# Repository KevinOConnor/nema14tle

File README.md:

This is an experimental pcb design for a TLE5012B angle sensor mounted
on the back of a NEMA14 stepper motor.

This is an experiment. There is no support for this project.

The original design of the board is from Voron user "JNP".

The PCB design files can be found in the [pcb/](pcb/) directory.  The
boards were designed using [KiCad](https://kicad.org/) and
manufactured using [JLC PCB](https://jlcpcb.com/).

There is some information on the magnet mounting procedure in the
[magnet document](docs/magnet.md).

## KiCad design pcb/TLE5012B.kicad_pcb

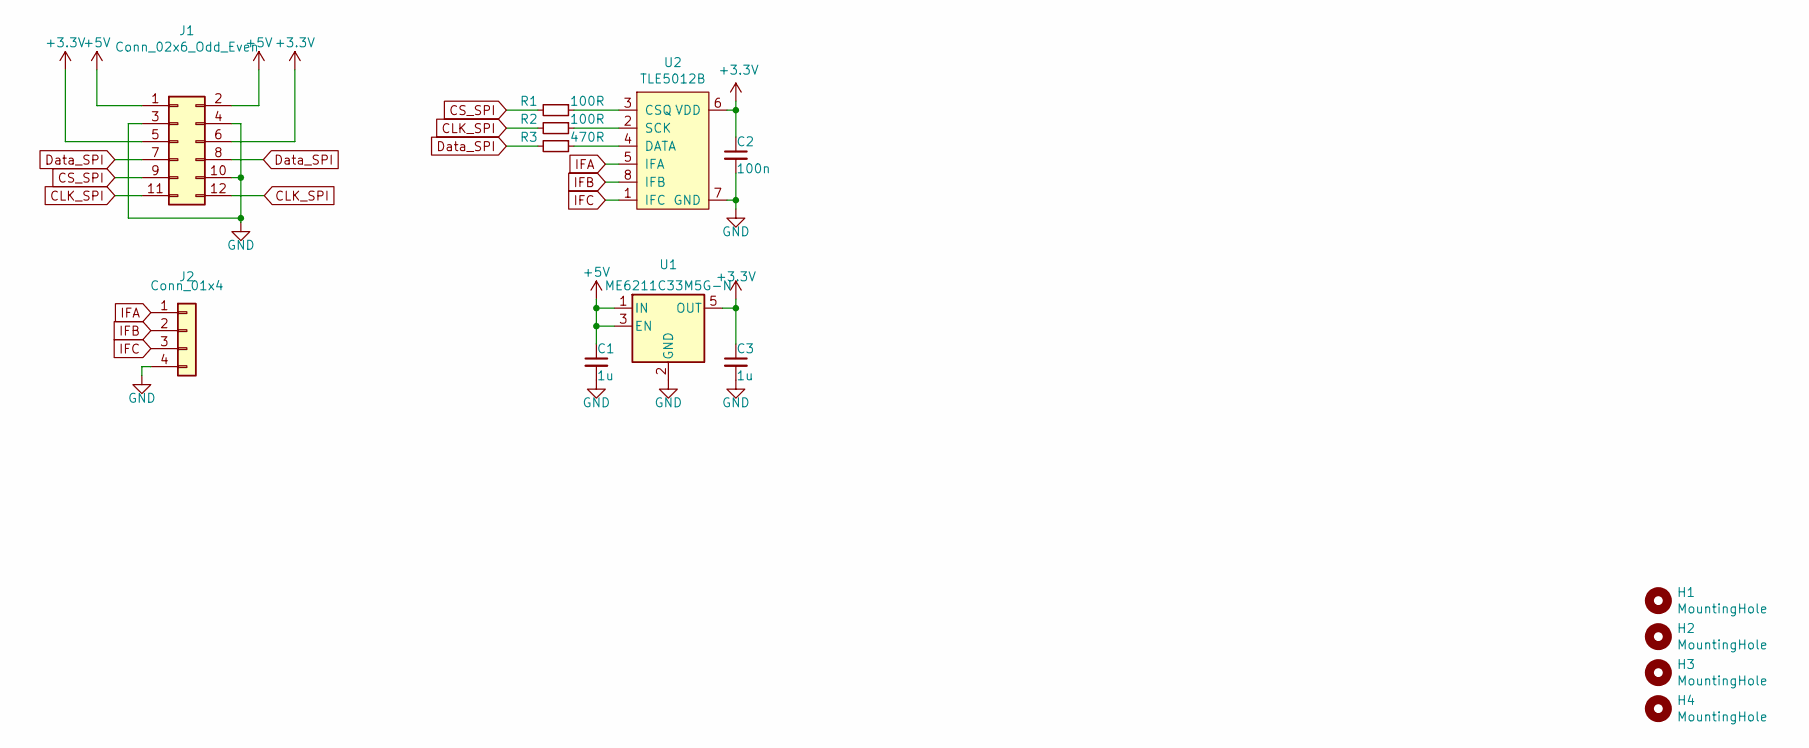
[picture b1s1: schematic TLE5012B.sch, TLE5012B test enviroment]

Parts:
C1, C3: 1u; C_0603_1608Metric; MFG# 0603B105K250NT; LCSC# C59302
C2: 100n; C_0603_1608Metric; LCSC# C14663
H1, H2, H3, H4: MountingHole; MountingHole_3.2mm_M3
J1: Conn_02x6_Odd_Even; PinHeader_2x06_P2.54mm_Vertical
J2: Conn_01x4; PinHeader_1x04_P2.54mm_Vertical
R1, R2: 100R; R_0603_1608Metric; MFG# MR06X1000FTL; LCSC# C327825
R3: 470R; R_0603_1608Metric; MFG# RS-03K4700FT; LCSC# C116694
U1: ME6211C33M5G-N; SOT-23-5; MFG# ME6211C33M5G-N; LCSC# C82942
U2: TLE5012B; Infineon_PG-DSO-8; LCSC# C123083

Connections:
+3V3: C2.1, C3.1, J1.5, J1.6, U1.5 (OUT), U2.6 (VDD)
+5V: C1.1, J1.1, J1.2, U1.1 (IN), U1.3 (EN)
CLK_SPI: J1.11, J1.12, R2.2
CS_SPI: J1.9, R1.2
Data_SPI: J1.7, J1.8, R3.2
GND: C1.2, C2.2, C3.2, J1.3, J1.4, J1.10, J2.4, U1.2 (GND), U2.7 (GND)
IFA: J2.1, U2.5 (IFA)
IFB: J2.2, U2.8 (IFB)
IFC: J2.3, U2.1 (IFC)
unnamed: R1.1, U2.3 (CSQ)
unnamed: R2.1, U2.2 (SCK)
unnamed: R3.1, U2.4 (DATA)

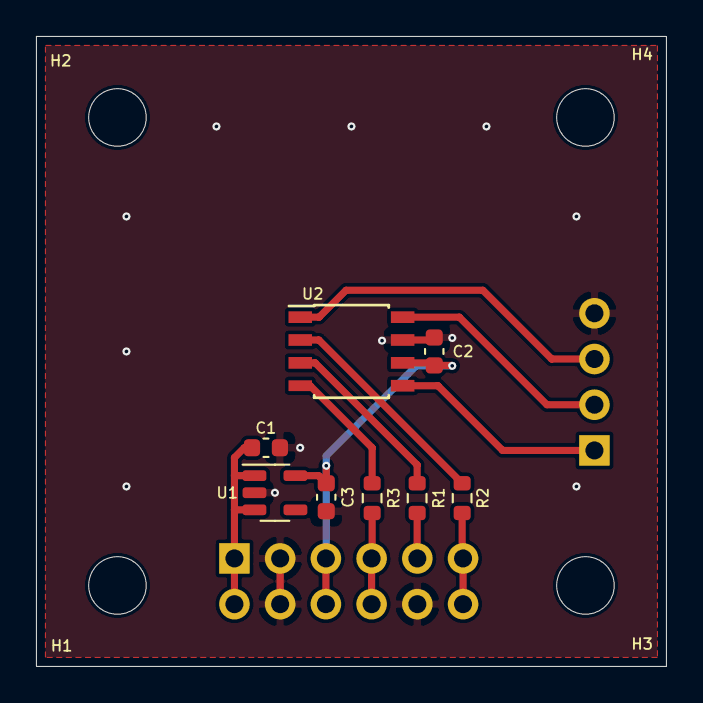
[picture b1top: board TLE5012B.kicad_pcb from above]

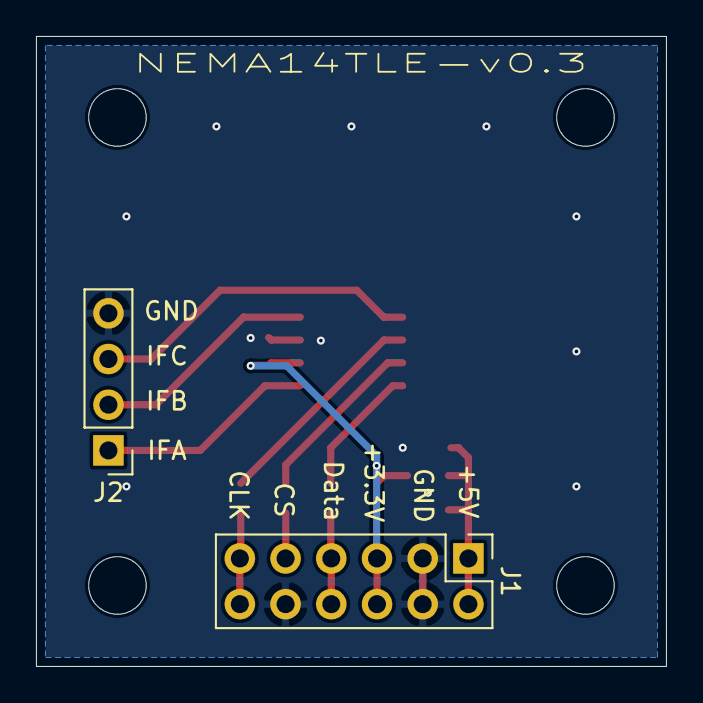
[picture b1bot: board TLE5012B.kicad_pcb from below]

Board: 2 copper layers, 35.0 x 35.0 mm, 14 parts (2 on the bottom side), 12 nets.

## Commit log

2021-06-17 Initial commit of board design by JNP.
2021-06-17 pcb: Minor updates to pcb
    Only have one CS pin header (ground the others).
    Add additional ground vias around perimeter of board.
    Update 100nF LCSC part number
2021-07-17 prints: Add model for 3d-printed stepper motor spacers
2021-07-17 prints: Add 3d-printer model for magnet attachment tool
2021-07-18 docs: Add picture of assembled motor and pcb
2021-07-18 docs: Add information on mounting of board and magnet
2021-07-18 docs: Add note about wiring complexity of current design
2021-11-07 Update README.md
    https://forum.kicad.info/t/warning-avoid-all-links-to-kicad-pcb-org-use-kicad-org/31521/
